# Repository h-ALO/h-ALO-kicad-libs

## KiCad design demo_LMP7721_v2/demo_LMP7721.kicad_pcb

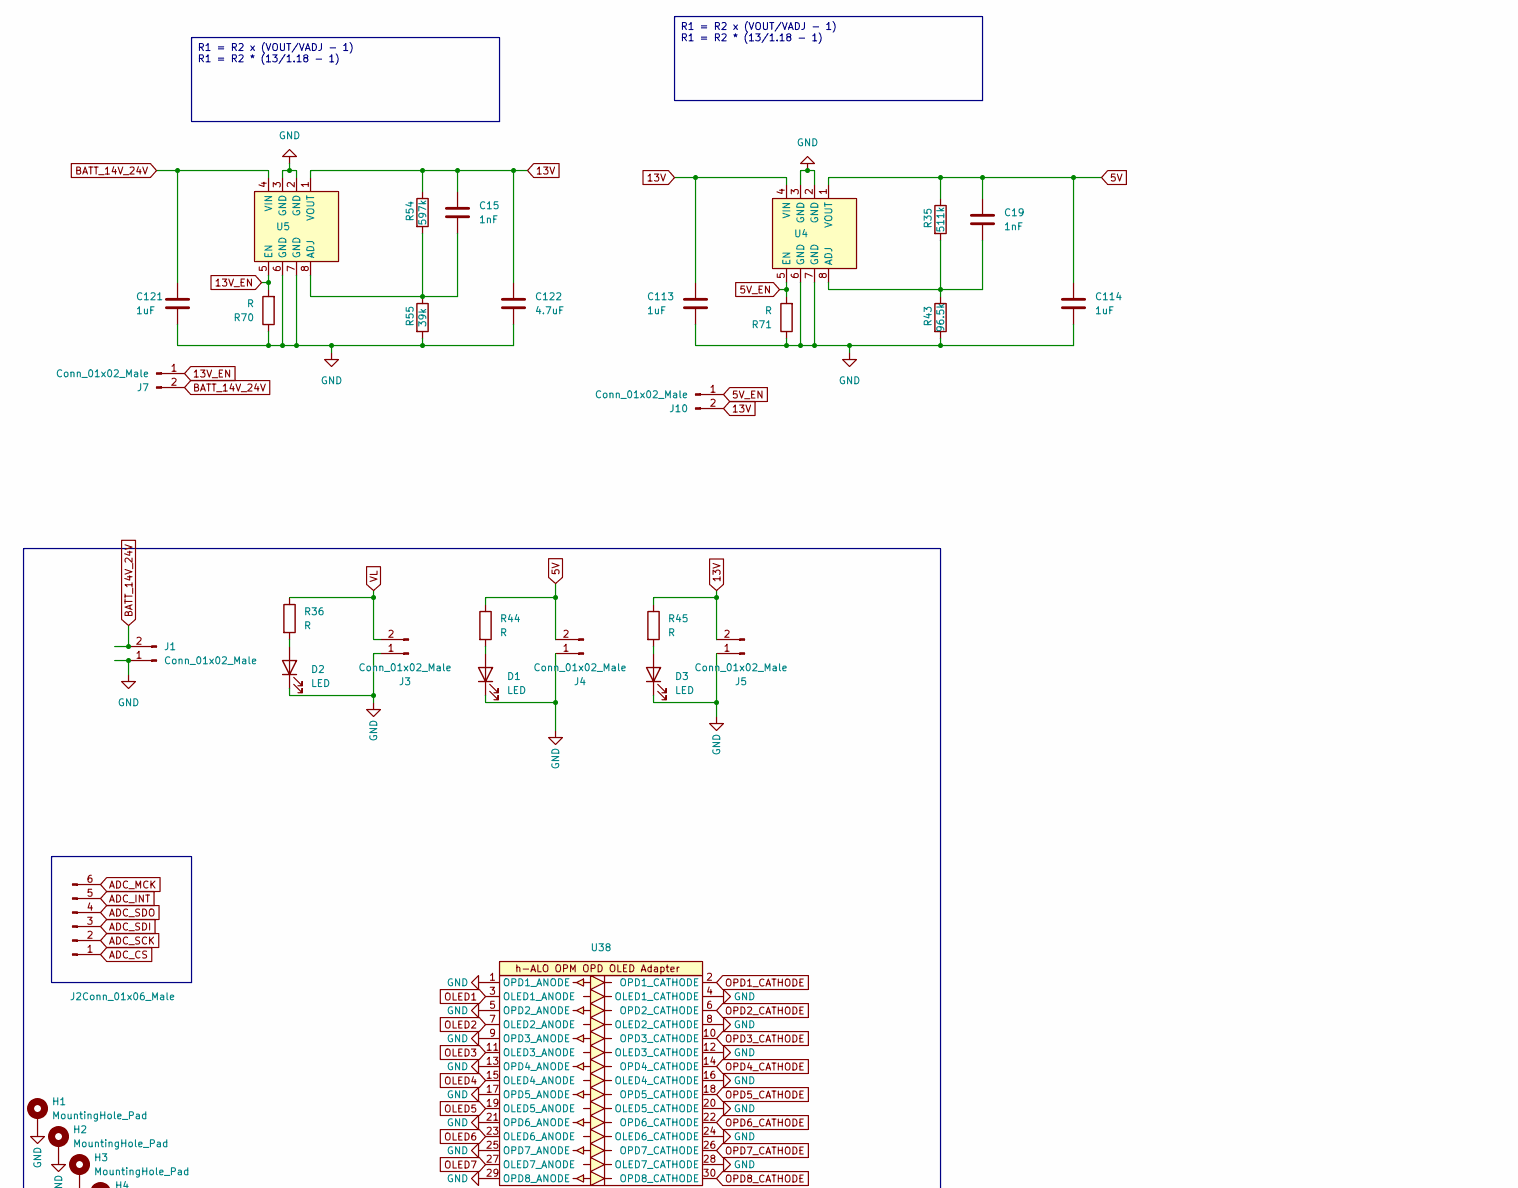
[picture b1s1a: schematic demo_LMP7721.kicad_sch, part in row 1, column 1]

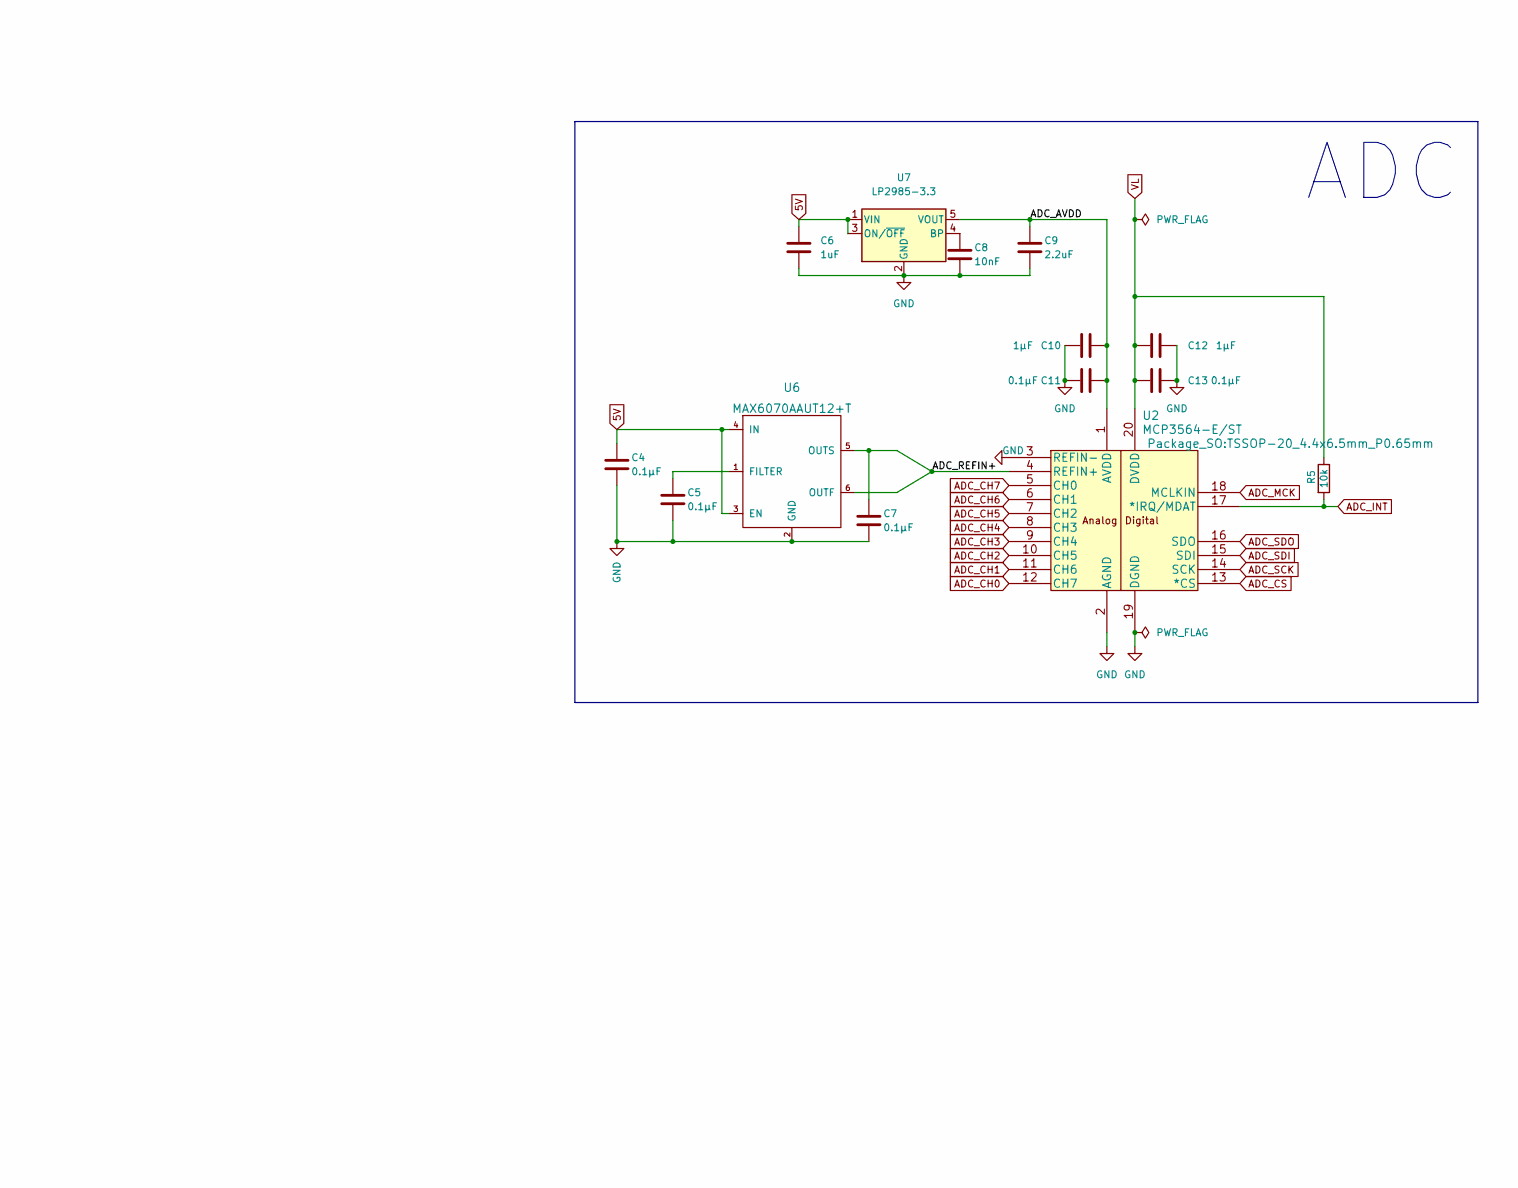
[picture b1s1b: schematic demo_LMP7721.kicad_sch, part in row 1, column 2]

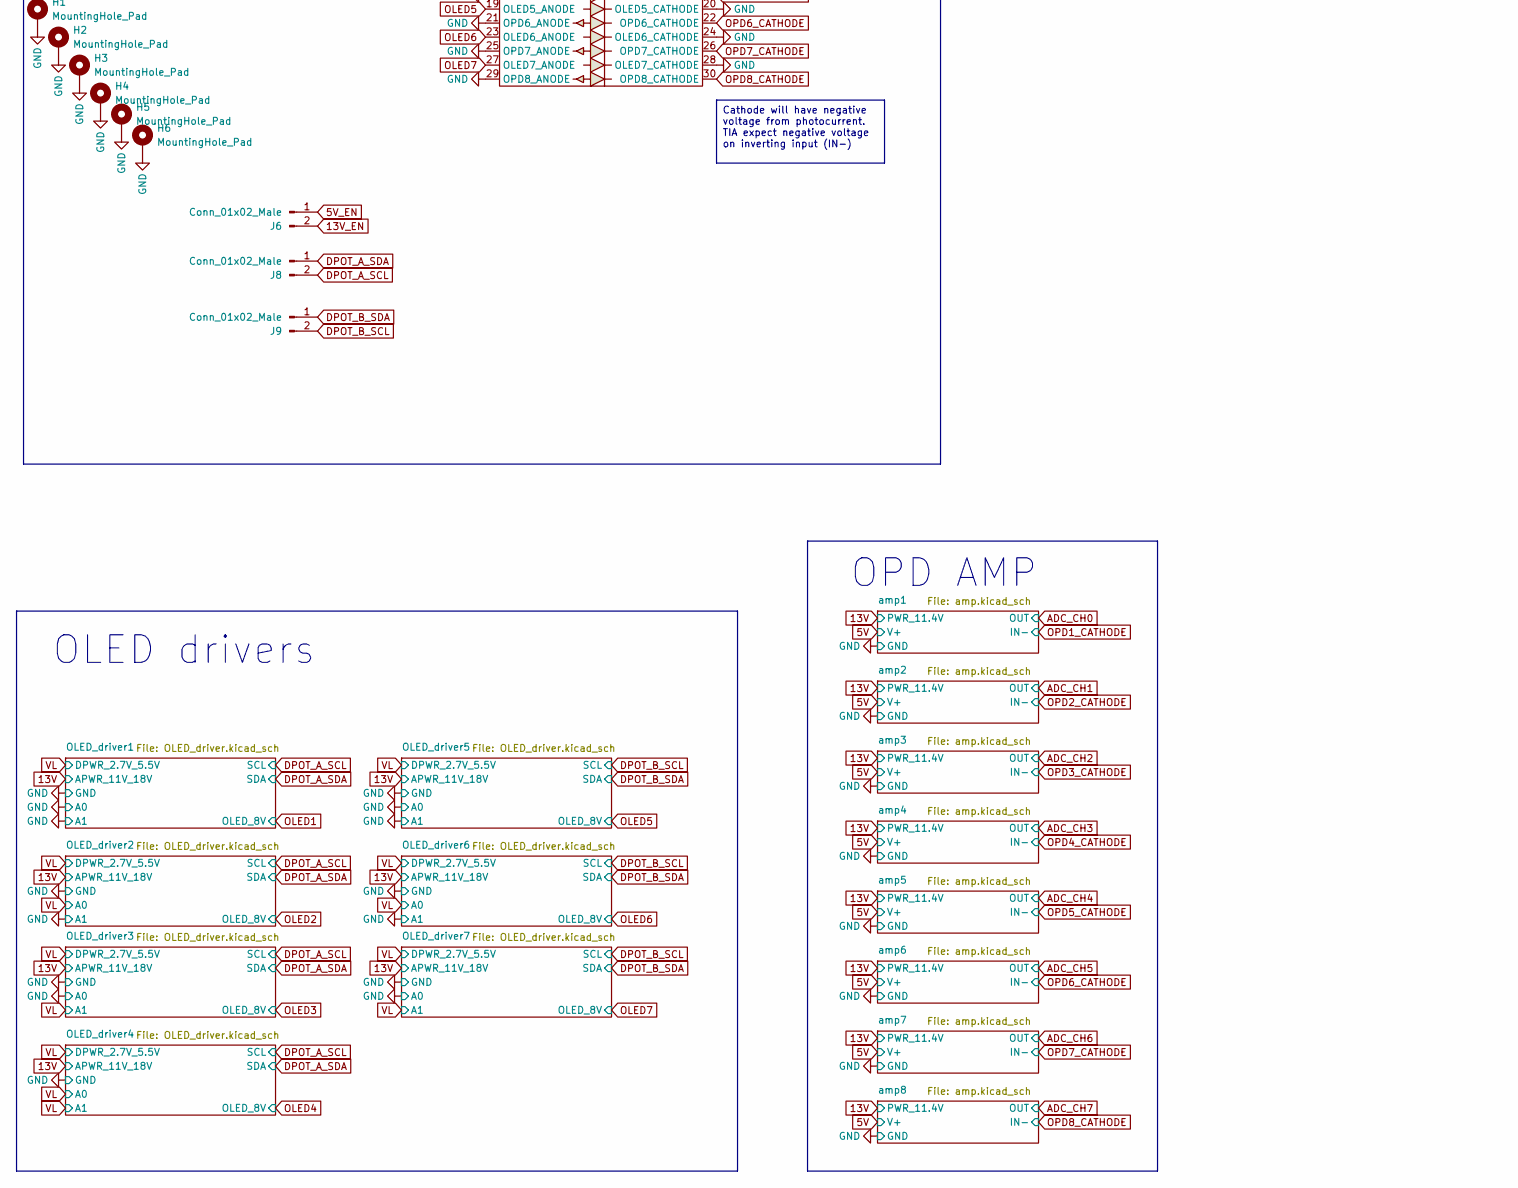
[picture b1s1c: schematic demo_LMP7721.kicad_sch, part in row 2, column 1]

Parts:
C4, C5, C7, C11, C13: 0.1µF; C_0603_1608Metric
C6: 1uF; C_0603_1608Metric
C8: 10nF; C_0603_1608Metric
C9: 2.2uF; C_0603_1608Metric
C10, C12: 1µF; C_0603_1608Metric
C15, C19: 1nF; C_0603_1608Metric
C113, C114, C121: 1uF; C_0805_2012Metric
C122: 4.7uF; C_0805_2012Metric
D1, D2, D3: LED; LED_0603_1608Metric
H1, H2, H3, H4, H5, H6: MountingHole_Pad; MountingHole_3.2mm_M3_Pad_Via
J1, J3, J4, J5, J6, J8, J9: Conn_01x02_Male; JST_XH_B2B-XH-A_1x02_P2.50mm_Vertical
J2: Conn_01x06_Male; JST_XH_B6B-XH-A_1x06_P2.50mm_Vertical
J7, J10: Conn_01x02_Male; PinHeader_1x02_P2.54mm_Vertical
R5: 10k; R_0603_1608Metric
R35: 511k; R_0603_1608Metric
R36, R44, R45, R70, R71: R; R_0603_1608Metric
R43: 96.5k; R_0603_1608Metric
R54: 597k; R_0603_1608Metric
R55: 39k; R_0603_1608Metric
U2: MCP3564-E/ST; TSSOP-20_4.4x6.5mm_P0.65mm
U4, U5: SOIC-8_3.9x4.9mm_P1.27mm
U6: MAX6070AAUT12+T; SOT-23-6
U7: LP2985-3.3; SOT-23-5
U38: OPM_Sensor_PinHeader_2x15_P2.54mm_Vertical

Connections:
5V: C4.1, C6.1, C19.1, C114.1, J4.2, R35.1, R44.1, U4.1 (VOUT), U6.3 (EN), U6.4 (IN), U7.1 (VIN), U7.3 (ON/~OFF); also elsewhere on the board
5V_EN: J6.1, J10.1, R71.2, U4.5 (EN)
13V: C15.1, C113.1, C122.1, J5.2, J10.2, R45.1, R54.1, U4.4 (VIN), U5.1 (VOUT); also elsewhere on the board
13V_EN: J6.2, J7.1, R70.2, U5.5 (EN)
/ADC_AVDD: C9.1, C10.2, C11.2, U2.1 (AVDD), U7.5 (VOUT)
/ADC_REFIN+: C7.1, U2.4 (REFIN+), U6.5 (OUTS), U6.6 (OUTF)
ADC_CH0: U2.12 (CH7); also elsewhere on the board
ADC_CH1: U2.11 (CH6); also elsewhere on the board
ADC_CH2: U2.10 (CH5); also elsewhere on the board
ADC_CH3: U2.9 (CH4); also elsewhere on the board
ADC_CH4: U2.8 (CH3); also elsewhere on the board
ADC_CH5: U2.7 (CH2); also elsewhere on the board
ADC_CH6: U2.6 (CH1); also elsewhere on the board
ADC_CH7: U2.5 (CH0); also elsewhere on the board
ADC_CS: J2.1, U2.13 (*CS)
ADC_INT: J2.5, R5.2, U2.17 (*IRQ/MDAT)
ADC_MCK: J2.6, U2.18 (MCLKIN)
ADC_SCK: J2.2, U2.14 (SCK)
ADC_SDI: J2.3, U2.15 (SDI)
ADC_SDO: J2.4, U2.16 (SDO)
BATT_14V_24V: C121.1, J1.2, J7.2, U5.4 (VIN)
DPOT_A_SCL: J8.2; also elsewhere on the board
DPOT_A_SDA: J8.1; also elsewhere on the board
DPOT_B_SCL: J9.2; also elsewhere on the board
DPOT_B_SDA: J9.1; also elsewhere on the board
GND: C4.2, C5.2, C6.2, C7.2, C8.2, C9.2, C10.1, C11.1, C12.2, C13.2, C113.2, C114.2, C121.2, C122.2, D1.1 (K), D2.1 (K), D3.1 (K), H1.1, H2.1, H3.1, H4.1, H5.1, H6.1, J1.1, J3.1, J4.1, J5.1, R43.2, R55.2, R70.1, R71.1, U2.2 (AGND), U2.3 (REFIN-), U2.19 (DGND), U4.2 (GND), U4.3 (GND), U4.6 (GND), U4.7 (GND), U5.2 (GND), U5.3 (GND), U5.6 (GND), U5.7 (GND), U6.2 (GND), U7.2 (GND), U38.1 (OPD1_ANODE), U38.4 (OLED1_CATHODE), U38.5 (OPD2_ANODE), U38.8 (OLED2_CATHODE), U38.9 (OPD3_ANODE), U38.12 (OLED3_CATHODE), U38.13 (OPD4_ANODE), U38.16 (OLED4_CATHODE), U38.17 (OPD5_ANODE), U38.20 (OLED5_CATHODE), U38.21 (OPD6_ANODE), U38.24 (OLED6_CATHODE), U38.25 (OPD7_ANODE), U38.28 (OLED7_CATHODE), U38.29 (OPD8_ANODE); also elsewhere on the board
unnamed: D1.2 (A), R44.2
unnamed: D2.2 (A), R36.2
unnamed: D3.2 (A), R45.2
unnamed: C19.2, R35.2, R43.1, U4.8 (ADJ)
unnamed: C15.2, R54.2, R55.1, U5.8 (ADJ)
unnamed: C5.1, U6.1 (FILTER)
unnamed: C8.1, U7.4 (BP)
OLED1: U38.3 (OLED1_ANODE); also elsewhere on the board
OLED2: U38.7 (OLED2_ANODE); also elsewhere on the board
OLED3: U38.11 (OLED3_ANODE); also elsewhere on the board
OLED4: U38.15 (OLED4_ANODE); also elsewhere on the board
OLED5: U38.19 (OLED5_ANODE); also elsewhere on the board
OLED6: U38.23 (OLED6_ANODE); also elsewhere on the board
OLED7: U38.27 (OLED7_ANODE); also elsewhere on the board
OPD1_CATHODE: U38.2 (OPD1_CATHODE); also elsewhere on the board
OPD2_CATHODE: U38.6 (OPD2_CATHODE); also elsewhere on the board
OPD3_CATHODE: U38.10 (OPD3_CATHODE); also elsewhere on the board
OPD4_CATHODE: U38.14 (OPD4_CATHODE); also elsewhere on the board
OPD5_CATHODE: U38.18 (OPD5_CATHODE); also elsewhere on the board
OPD6_CATHODE: U38.22 (OPD6_CATHODE); also elsewhere on the board
OPD7_CATHODE: U38.26 (OPD7_CATHODE); also elsewhere on the board
OPD8_CATHODE: U38.30 (OPD8_CATHODE); also elsewhere on the board
VL: C12.1, C13.1, J3.2, R5.1, R36.1, U2.20 (DVDD); also elsewhere on the board

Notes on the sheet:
R1 = R2 x (VOUT/VADJ - 1) R1 = R2 * (13/1.18 - 1)
Cathode will have negative voltage from photocurrent. TIA expect negative voltage on inverting input (IN-)
OPD AMP
ADC
OLED drivers

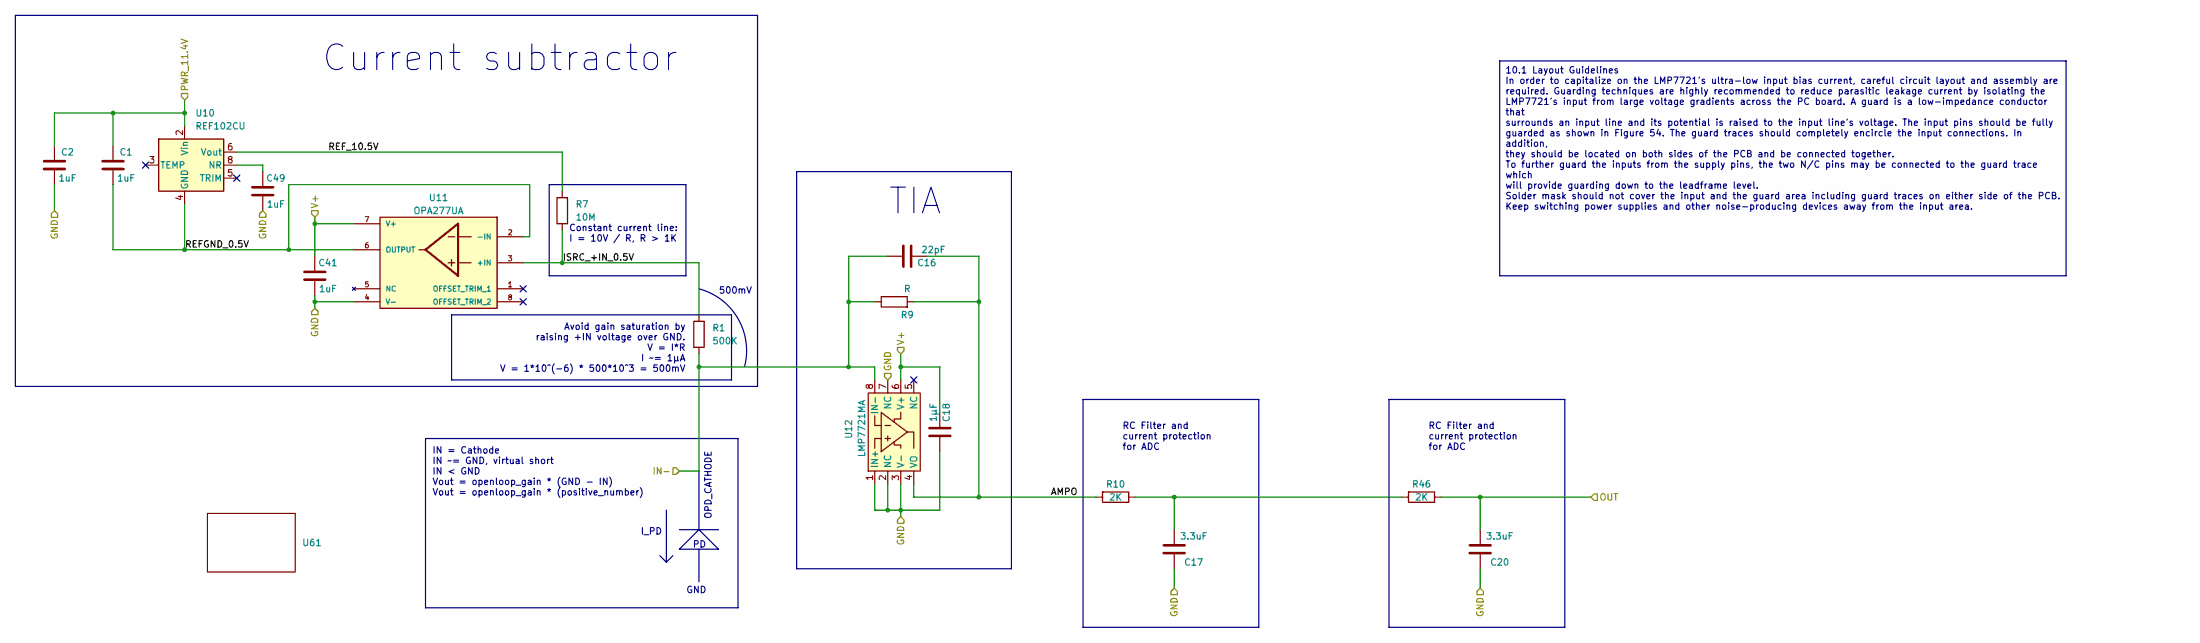
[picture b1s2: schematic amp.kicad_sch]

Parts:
C1, C2, C41, C49: 1uF; C_0603_1608Metric
C16: 22pF; FB_C_0603_1608Metric
C17, C20: 3.3uF; C_0603_1608Metric
C18: 1µF; C_0603_1608Metric
R1: 500K; TIA_R_0603_1608Metric
R7: 10M; R_0603_1608Metric
R9: R; FB_R_1206_3216Metric
R10, R46: 2K; R_0603_1608Metric
U10: REF102CU; SOIC-8_3.9x4.9mm_P1.27mm
U11: OPA277UA; TIA_OPA277_SOIC-8_3.9x4.9mm_P1.27mm; PARTREV 02/2019
U12: LMP7721MA; TIA_OPAMP_SOIC-8_3.9x4.9mm_P1.27mm
U61: OPD_TIA_Outline

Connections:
5V: C18.2, C41.2, U11.7 (V+), U12.6 (V+); also elsewhere on the board
13V: C1.2, C2.2, U10.2 (Vin); also elsewhere on the board
/amp1/AMPO: C16.2, R9.2, R10.2, U12.4 (VO)
/amp1/ISRC_+IN_0.5V: R1.2, R7.1, U11.3 (+IN)
/amp1/REFGND_0.5V: C1.1, U10.4 (GND), U11.2 (-IN), U11.6 (OUTPUT)
/amp1/REF_10.5V: R7.2, U10.6 (Vout)
ADC_CH0: C20.2, R46.1; also elsewhere on the board
GND: C2.1, C17.1, C18.1, C20.1, C41.1, C49.1, U11.4 (V-), U12.1 (IN+), U12.2 (NC), U12.3 (V-), U12.7 (NC); also elsewhere on the board
unnamed: C17.2, R10.1, R46.2
unnamed: C49.2, U10.8 (NR)
OPD1_CATHODE: C16.1, R1.1, R9.1, U12.8 (IN-); also elsewhere on the board

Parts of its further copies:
C21, C28, C40, C53, C97, C104, C111, C112, C115, C116, C117, C118, C119, C120: 3.3uF; C_0603_1608Metric
C22, C23, C24, C25, C29, C35, C36, C37, C42, C43, C44, C45, C55, C57, C61, C62, C84, C85, C86, C87, C98, C99, C100, C101, C105, C106, C107, C108: 1uF; C_0603_1608Metric
C26, C38, C47, C63, C88, C102, C109: 22pF; FB_C_0603_1608Metric
C27, C39, C51, C64, C96, C103, C110: 1µF; C_0603_1608Metric
R2, R14, R19, R25, R27, R30, R34: 10M; R_0603_1608Metric
R3, R15, R21, R26, R31, R37, R40: 500K; TIA_R_0603_1608Metric
R11, R17, R22, R28, R32, R38, R41: R; FB_R_1206_3216Metric
R13, R18, R23, R29, R33, R39, R42, R47, R48, R49, R50, R51, R52, R53: 2K; R_0603_1608Metric
U3, U17, U20, U23, U45, U48, U51: REF102CU; SOIC-8_3.9x4.9mm_P1.27mm
U15, U18, U21, U24, U46, U49, U52: OPA277UA; TIA_OPA277_SOIC-8_3.9x4.9mm_P1.27mm; PARTREV 02/2019
U16, U19, U22, U36, U47, U50, U53: LMP7721MA; TIA_OPAMP_SOIC-8_3.9x4.9mm_P1.27mm
U62, U63, U64, U65, U66, U67, U68: OPD_TIA_Outline

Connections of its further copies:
5V: C25.2, C27.2, C37.2, C39.2, C45.2, C51.2, C62.2, C64.2, C87.2, C96.2, C101.2, C103.2, C108.2, C110.2, U15.7 (V+), U16.6 (V+), U18.7 (V+), U19.6 (V+), U21.7 (V+), U22.6 (V+), U24.7 (V+), U36.6 (V+), U46.7 (V+), U47.6 (V+), U49.7 (V+), U50.6 (V+), U52.7 (V+), U53.6 (V+); also elsewhere on the board
13V: C22.2, C23.2, C29.2, C35.2, C42.2, C43.2, C55.2, C57.2, C84.2, C85.2, C98.2, C99.2, C105.2, C106.2, U3.2 (Vin), U17.2 (Vin), U20.2 (Vin), U23.2 (Vin), U45.2 (Vin), U48.2 (Vin), U51.2 (Vin); also elsewhere on the board
/amp2/AMPO: C26.2, R11.2, R13.2, U16.4 (VO)
/amp2/ISRC_+IN_0.5V: R2.1, R3.2, U15.3 (+IN)
/amp2/REFGND_0.5V: C23.1, U3.4 (GND), U15.2 (-IN), U15.6 (OUTPUT)
/amp2/REF_10.5V: R2.2, U3.6 (Vout)
/amp3/AMPO: C38.2, R17.2, R18.2, U19.4 (VO)
/amp3/ISRC_+IN_0.5V: R14.1, R15.2, U18.3 (+IN)
/amp3/REFGND_0.5V: C35.1, U17.4 (GND), U18.2 (-IN), U18.6 (OUTPUT)
/amp3/REF_10.5V: R14.2, U17.6 (Vout)
/amp4/AMPO: C47.2, R22.2, R23.2, U22.4 (VO)
/amp4/ISRC_+IN_0.5V: R19.1, R21.2, U21.3 (+IN)
/amp4/REFGND_0.5V: C43.1, U20.4 (GND), U21.2 (-IN), U21.6 (OUTPUT)
/amp4/REF_10.5V: R19.2, U20.6 (Vout)
/amp5/AMPO: C63.2, R28.2, R29.2, U36.4 (VO)
/amp5/ISRC_+IN_0.5V: R25.1, R26.2, U24.3 (+IN)
/amp5/REFGND_0.5V: C57.1, U23.4 (GND), U24.2 (-IN), U24.6 (OUTPUT)
/amp5/REF_10.5V: R25.2, U23.6 (Vout)
/amp6/AMPO: C102.2, R32.2, R33.2, U50.4 (VO)
/amp6/ISRC_+IN_0.5V: R30.1, R31.2, U49.3 (+IN)
/amp6/REFGND_0.5V: C99.1, U48.4 (GND), U49.2 (-IN), U49.6 (OUTPUT)
/amp6/REF_10.5V: R30.2, U48.6 (Vout)
/amp7/AMPO: C109.2, R38.2, R39.2, U53.4 (VO)
/amp7/ISRC_+IN_0.5V: R34.1, R37.2, U52.3 (+IN)
/amp7/REFGND_0.5V: C106.1, U51.4 (GND), U52.2 (-IN), U52.6 (OUTPUT)
/amp7/REF_10.5V: R34.2, U51.6 (Vout)
/amp8/AMPO: C88.2, R41.2, R42.2, U47.4 (VO)
/amp8/ISRC_+IN_0.5V: R27.1, R40.2, U46.3 (+IN)
/amp8/REFGND_0.5V: C85.1, U45.4 (GND), U46.2 (-IN), U46.6 (OUTPUT)
/amp8/REF_10.5V: R27.2, U45.6 (Vout)
ADC_CH1: C21.2, R47.1; also elsewhere on the board
ADC_CH2: C115.2, R48.1; also elsewhere on the board
ADC_CH3: C116.2, R49.1; also elsewhere on the board
ADC_CH4: C117.2, R50.1; also elsewhere on the board
ADC_CH5: C118.2, R51.1; also elsewhere on the board
ADC_CH6: C119.2, R52.1; also elsewhere on the board
ADC_CH7: C120.2, R53.1; also elsewhere on the board
GND: C21.1, C22.1, C24.1, C25.1, C27.1, C28.1, C29.1, C36.1, C37.1, C39.1, C40.1, C42.1, C44.1, C45.1, C51.1, C53.1, C55.1, C61.1, C62.1, C64.1, C84.1, C86.1, C87.1, C96.1, C97.1, C98.1, C100.1, C101.1, C103.1, C104.1, C105.1, C107.1, C108.1, C110.1, C111.1, C112.1, C115.1, C116.1, C117.1, C118.1, C119.1, C120.1, U15.4 (V-), U16.1 (IN+), U16.2 (NC), U16.3 (V-), U16.7 (NC), U18.4 (V-), U19.1 (IN+), U19.2 (NC), U19.3 (V-), U19.7 (NC), U21.4 (V-), U22.1 (IN+), U22.2 (NC), U22.3 (V-), U22.7 (NC), U24.4 (V-), U36.1 (IN+), U36.2 (NC), U36.3 (V-), U36.7 (NC), U46.4 (V-), U47.1 (IN+), U47.2 (NC), U47.3 (V-), U47.7 (NC), U49.4 (V-), U50.1 (IN+), U50.2 (NC), U50.3 (V-), U50.7 (NC), U52.4 (V-), U53.1 (IN+), U53.2 (NC), U53.3 (V-), U53.7 (NC); also elsewhere on the board
unnamed: C28.2, R13.1, R47.2
unnamed: C40.2, R18.1, R48.2
unnamed: C53.2, R23.1, R49.2
unnamed: C97.2, R29.1, R50.2
unnamed: C104.2, R33.1, R51.2
unnamed: C111.2, R39.1, R52.2
unnamed: C112.2, R42.1, R53.2
unnamed: C24.2, U3.8 (NR)
unnamed: C36.2, U17.8 (NR)
unnamed: C44.2, U20.8 (NR)
unnamed: C61.2, U23.8 (NR)
unnamed: C86.2, U45.8 (NR)
unnamed: C100.2, U48.8 (NR)
unnamed: C107.2, U51.8 (NR)
OPD2_CATHODE: C26.1, R3.1, R11.1, U16.8 (IN-); also elsewhere on the board
OPD3_CATHODE: C38.1, R15.1, R17.1, U19.8 (IN-); also elsewhere on the board
OPD4_CATHODE: C47.1, R21.1, R22.1, U22.8 (IN-); also elsewhere on the board
OPD5_CATHODE: C63.1, R26.1, R28.1, U36.8 (IN-); also elsewhere on the board
OPD6_CATHODE: C102.1, R31.1, R32.1, U50.8 (IN-); also elsewhere on the board
OPD7_CATHODE: C109.1, R37.1, R38.1, U53.8 (IN-); also elsewhere on the board
OPD8_CATHODE: C88.1, R40.1, R41.1, U47.8 (IN-); also elsewhere on the board

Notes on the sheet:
10.1 Layout Guidelines In order to capitalize on the LMP7721's ultra-low input bias current, careful circuit layout and assembly are required. Guarding techniques are highly recommended to reduce parasitic leakage current by isolating the LMP7721's input from large voltage gradients across the PC b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
I_PD
Constant current line: I = 10V / R, R > 1K
TIA
RC Filter and current protection for ADC
GND
Avoid gain saturation by raising +IN voltage over GND. V = I*R I ~= 1µA V = 1*10^(-6) * 500*10^3 = 500mV
IN = Cathode IN ~= GND, virtual short IN < GND Vout = openloop_gain * (GND - IN) Vout = openloop_gain * (positive_number)
500mV
OPD_CATHODE
Current subtractor

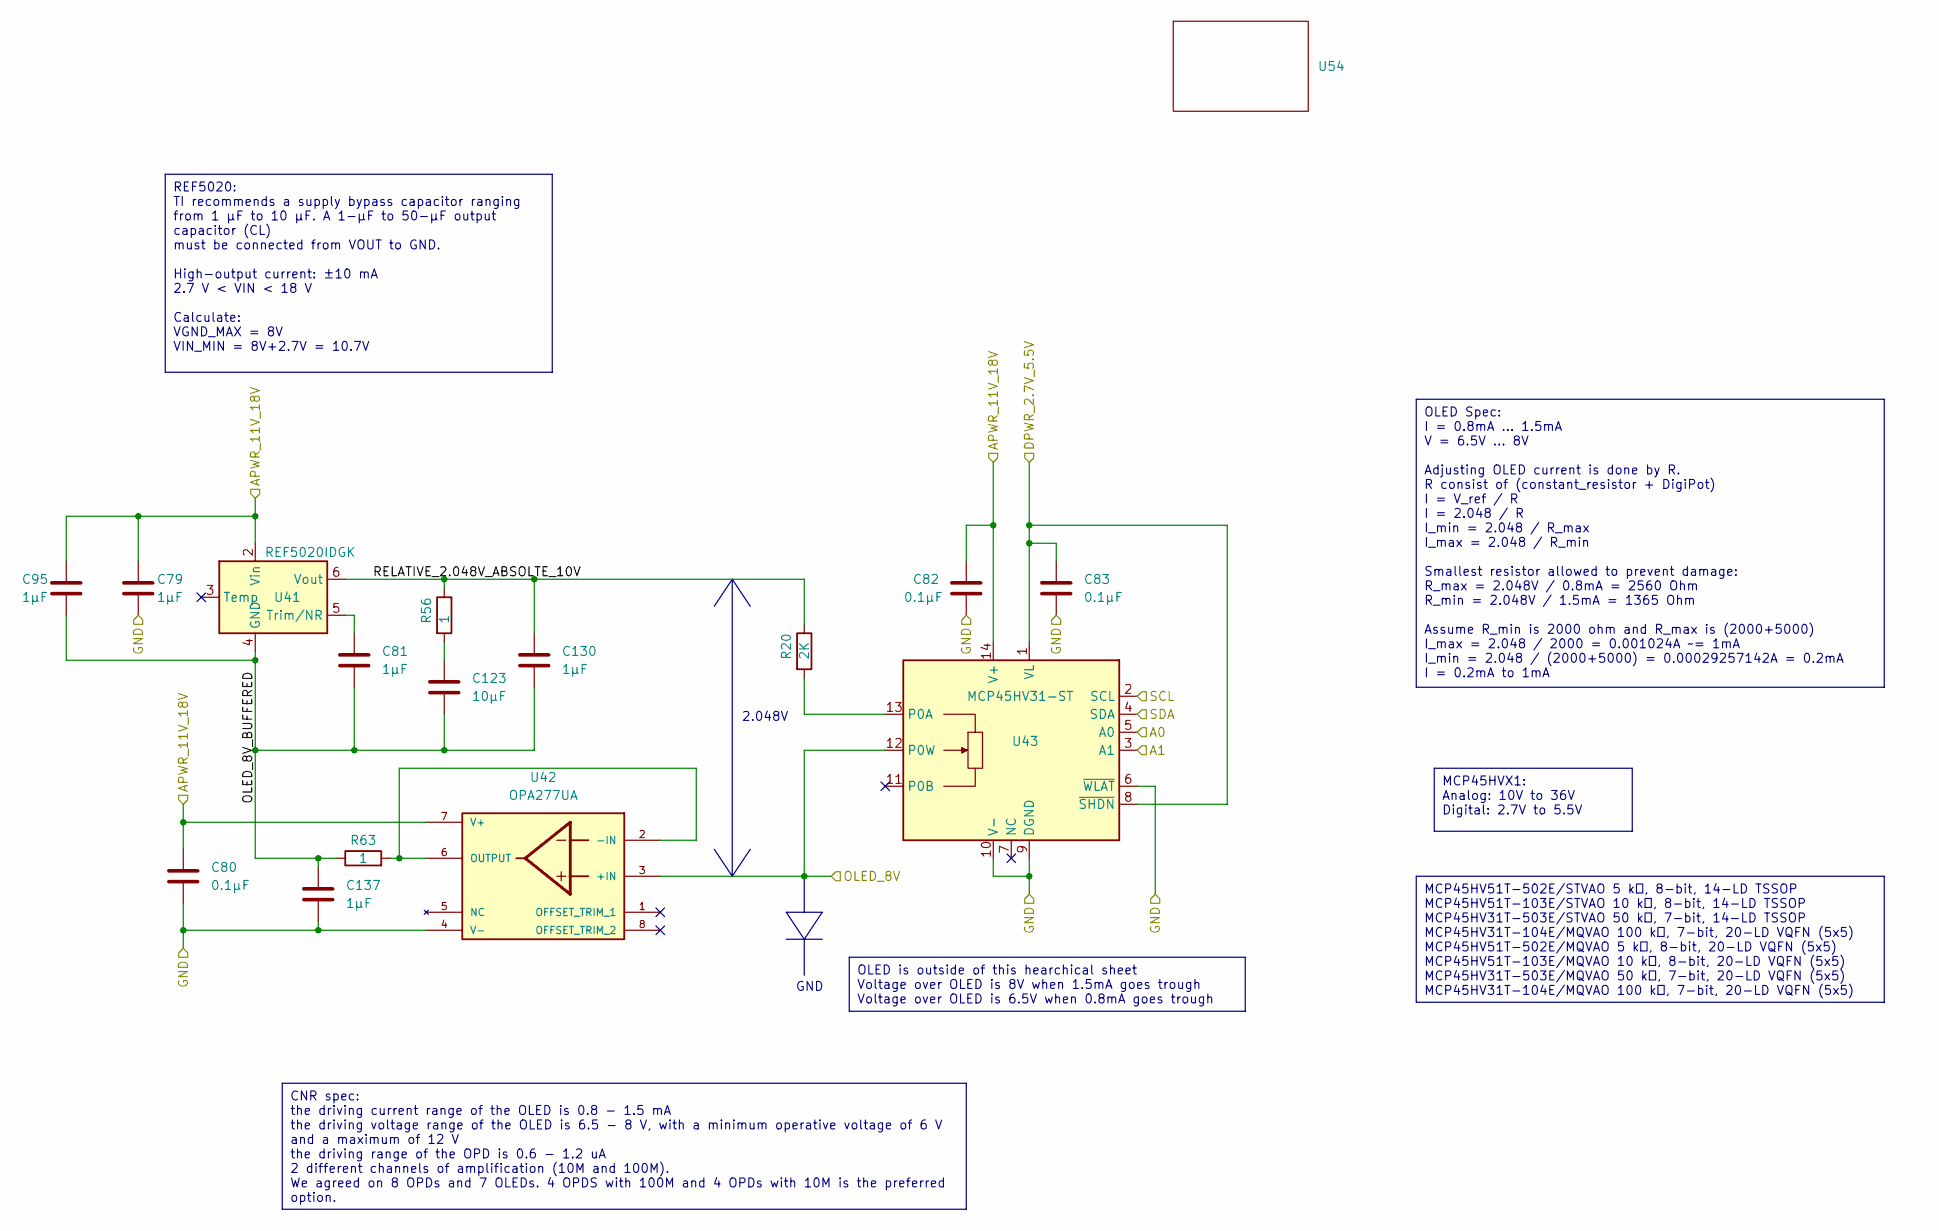
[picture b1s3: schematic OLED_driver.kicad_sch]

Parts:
C79, C81, C95, C130, C137: 1µF; C_0603_1608Metric
C80, C82, C83: 0.1μF; C_0603_1608Metric
C123: 10µF; C_1206_3216Metric
R20: 2K; R_0603_1608Metric
R56, R63: 1; R_0603_1608Metric
U41: REF5020IDGK; MSOP-8_3x3mm_P0.65mm
U42: OPA277UA; SOIC-8_3.9x4.9mm_P1.27mm; PARTREV 02/2019
U43: MCP45HV31-ST; TSSOP-14_4.4x5mm_P0.65mm
U54: OLED_Driver_Outline

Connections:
13V: C79.1, C80.1, C82.1, C95.1, U41.2 (Vin), U42.7 (V+), U43.14 (V+); also elsewhere on the board
/OLED_driver1/OLED_8V_BUFFERED: C81.2, C95.2, C123.2, C130.2, C137.1, R63.1, U41.4 (GND)
/OLED_driver1/RELATIVE_2.048V_ABSOLTE_10V: C130.1, R20.1, R56.1, U41.6 (Vout)
DPOT_A_SCL: U43.2 (SCL); also elsewhere on the board
DPOT_A_SDA: U43.4 (SDA); also elsewhere on the board
GND: C79.2, C80.2, C82.2, C83.2, C137.2, U42.4 (V-), U43.3 (A1), U43.5 (A0), U43.6 (~WLAT), U43.9 (DGND), U43.10 (V-); also elsewhere on the board
unnamed: C123.1, R56.2
unnamed: C81.1, U41.5 (Trim/NR)
unnamed: R63.2, U42.2 (-IN), U42.6 (OUTPUT)
unnamed: R20.2, U43.13 (P0A)
OLED1: U42.3 (+IN), U43.12 (P0W); also elsewhere on the board
VL: C83.1, U43.1 (VL), U43.8 (~SHDN); also elsewhere on the board

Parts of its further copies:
C3, C30, C33, C46, C52, C56, C60, C66, C69, C71, C74, C76, C89, C90, C91, C92, C93, C94, C131, C132, C133, C134, C135, C136, C138, C139, C140, C141, C142, C143: 1µF; C_0603_1608Metric
C14, C31, C32, C34, C48, C50, C54, C58, C59, C65, C67, C68, C70, C72, C73, C75, C77, C78: 0.1μF; C_0603_1608Metric
C124, C125, C126, C127, C128, C129: 10µF; C_1206_3216Metric
R4, R6, R8, R12, R16, R24: 2K; R_0603_1608Metric
R57, R58, R59, R60, R61, R62, R64, R65, R66, R67, R68, R69: 1; R_0603_1608Metric
U1, U25, U28, U31, U34, U39: REF5020IDGK; MSOP-8_3x3mm_P0.65mm
U8, U26, U29, U32, U35, U40: OPA277UA; SOIC-8_3.9x4.9mm_P1.27mm; PARTREV 02/2019
U9, U27, U30, U33, U37, U44: MCP45HV31-ST; TSSOP-14_4.4x5mm_P0.65mm
U55, U56, U57, U58, U59, U60: OLED_Driver_Outline

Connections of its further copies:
13V: C3.1, C14.1, C31.1, C33.1, C34.1, C48.1, C52.1, C54.1, C58.1, C60.1, C65.1, C67.1, C69.1, C70.1, C72.1, C74.1, C75.1, C77.1, C89.1, C90.1, C91.1, C92.1, C93.1, C94.1, U1.2 (Vin), U8.7 (V+), U9.14 (V+), U25.2 (Vin), U26.7 (V+), U27.14 (V+), U28.2 (Vin), U29.7 (V+), U30.14 (V+), U31.2 (Vin), U32.7 (V+), U33.14 (V+), U34.2 (Vin), U35.7 (V+), U37.14 (V+), U39.2 (Vin), U40.7 (V+), U44.14 (V+); also elsewhere on the board
/OLED_driver2/OLED_8V_BUFFERED: C30.2, C89.2, C124.2, C131.2, C138.1, R64.1, U1.4 (GND)
/OLED_driver2/RELATIVE_2.048V_ABSOLTE_10V: C131.1, R4.1, R57.1, U1.6 (Vout)
/OLED_driver3/OLED_8V_BUFFERED: C46.2, C90.2, C125.2, C132.2, C139.1, R65.1, U25.4 (GND)
/OLED_driver3/RELATIVE_2.048V_ABSOLTE_10V: C132.1, R6.1, R58.1, U25.6 (Vout)
/OLED_driver4/OLED_8V_BUFFERED: C56.2, C91.2, C126.2, C133.2, C140.1, R66.1, U28.4 (GND)
/OLED_driver4/RELATIVE_2.048V_ABSOLTE_10V: C133.1, R8.1, R59.1, U28.6 (Vout)
/OLED_driver5/OLED_8V_BUFFERED: C71.2, C93.2, C127.2, C134.2, C141.1, R67.1, U34.4 (GND)
/OLED_driver5/RELATIVE_2.048V_ABSOLTE_10V: C134.1, R16.1, R60.1, U34.6 (Vout)
/OLED_driver6/OLED_8V_BUFFERED: C76.2, C94.2, C128.2, C135.2, C142.1, R68.1, U39.4 (GND)
/OLED_driver6/RELATIVE_2.048V_ABSOLTE_10V: C135.1, R24.1, R61.1, U39.6 (Vout)
/OLED_driver7/OLED_8V_BUFFERED: C66.2, C92.2, C129.2, C136.2, C143.1, R69.1, U31.4 (GND)
/OLED_driver7/RELATIVE_2.048V_ABSOLTE_10V: C136.1, R12.1, R62.1, U31.6 (Vout)
DPOT_A_SCL: U9.2 (SCL), U27.2 (SCL), U30.2 (SCL); also elsewhere on the board
DPOT_A_SDA: U9.4 (SDA), U27.4 (SDA), U30.4 (SDA); also elsewhere on the board
DPOT_B_SCL: U33.2 (SCL), U37.2 (SCL), U44.2 (SCL); also elsewhere on the board
DPOT_B_SDA: U33.4 (SDA), U37.4 (SDA), U44.4 (SDA); also elsewhere on the board
GND: C3.2, C14.2, C31.2, C32.2, C33.2, C34.2, C48.2, C50.2, C52.2, C54.2, C58.2, C59.2, C60.2, C65.2, C67.2, C68.2, C69.2, C70.2, C72.2, C73.2, C74.2, C75.2, C77.2, C78.2, C138.2, C139.2, C140.2, C141.2, C142.2, C143.2, U8.4 (V-), U9.3 (A1), U9.6 (~WLAT), U9.9 (DGND), U9.10 (V-), U26.4 (V-), U27.5 (A0), U27.6 (~WLAT), U27.9 (DGND), U27.10 (V-), U29.4 (V-), U30.6 (~WLAT), U30.9 (DGND), U30.10 (V-), U32.4 (V-), U33.5 (A0), U33.6 (~WLAT), U33.9 (DGND), U33.10 (V-), U35.4 (V-), U37.3 (A1), U37.5 (A0), U37.6 (~WLAT), U37.9 (DGND), U37.10 (V-), U40.4 (V-), U44.3 (A1), U44.6 (~WLAT), U44.9 (DGND), U44.10 (V-); also elsewhere on the board
unnamed: C124.1, R57.2
unnamed: C125.1, R58.2
unnamed: C126.1, R59.2
unnamed: C127.1, R60.2
unnamed: C128.1, R61.2
unnamed: C129.1, R62.2
unnamed: C30.1, U1.5 (Trim/NR)
unnamed: R64.2, U8.2 (-IN), U8.6 (OUTPUT)
unnamed: R4.2, U9.13 (P0A)
unnamed: C46.1, U25.5 (Trim/NR)
unnamed: R65.2, U26.2 (-IN), U26.6 (OUTPUT)
unnamed: R6.2, U27.13 (P0A)
unnamed: C56.1, U28.5 (Trim/NR)
unnamed: R66.2, U29.2 (-IN), U29.6 (OUTPUT)
unnamed: R8.2, U30.13 (P0A)
unnamed: C66.1, U31.5 (Trim/NR)
unnamed: R69.2, U32.2 (-IN), U32.6 (OUTPUT)
unnamed: R12.2, U33.13 (P0A)
unnamed: C71.1, U34.5 (Trim/NR)
unnamed: R67.2, U35.2 (-IN), U35.6 (OUTPUT)
unnamed: R16.2, U37.13 (P0A)
unnamed: C76.1, U39.5 (Trim/NR)
unnamed: R68.2, U40.2 (-IN), U40.6 (OUTPUT)
unnamed: R24.2, U44.13 (P0A)
OLED2: U8.3 (+IN), U9.12 (P0W); also elsewhere on the board
OLED3: U26.3 (+IN), U27.12 (P0W); also elsewhere on the board
OLED4: U29.3 (+IN), U30.12 (P0W); also elsewhere on the board
OLED5: U35.3 (+IN), U37.12 (P0W); also elsewhere on the board
OLED6: U40.3 (+IN), U44.12 (P0W); also elsewhere on the board
OLED7: U32.3 (+IN), U33.12 (P0W); also elsewhere on the board
VL: C32.1, C50.1, C59.1, C68.1, C73.1, C78.1, U9.1 (VL), U9.5 (A0), U9.8 (~SHDN), U27.1 (VL), U27.3 (A1), U27.8 (~SHDN), U30.1 (VL), U30.3 (A1), U30.5 (A0), U30.8 (~SHDN), U33.1 (VL), U33.3 (A1), U33.8 (~SHDN), U37.1 (VL), U37.8 (~SHDN), U44.1 (VL), U44.5 (A0), U44.8 (~SHDN); also elsewhere on the board

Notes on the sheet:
OLED is outside of this hearchical sheet Voltage over OLED is 8V when 1.5mA goes trough Voltage over OLED is 6.5V when 0.8mA goes trough
CNR spec: the driving current range of the OLED is 0.8 - 1.5 mA the driving voltage range of the OLED is 6.5 - 8 V, with a minimum operative voltage of 6 V and a maximum of 12 V the driving range of the OPD is 0.6 - 1.2 uA 2 different channels of amplification (10M and 100M). We agreed on 8 OPDs an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
MCP45HV51T-502E/STVAO 5 k, 8-bit, 14-LD TSSOP MCP45HV51T-103E/STVAO 10 k, 8-bit, 14-LD TSSOP MCP45HV31T-503E/STVAO 50 k, 7-bit, 14-LD TSSOP MCP45HV31T-104E/MQVAO 100 k, 7-bit, 20-LD VQFN (5x5) MCP45HV51T-502E/MQVAO 5 k, 8-bit, 20-LD VQFN (5x5) MCP45HV51T-103E/MQVAO 10 k, 8-bit, 20-LD VQFN (5x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
OLED Spec: I = 0.8mA ... 1.5mA V = 6.5V ... 8V Adjusting OLED current is done by R. R consist of (constant_resistor + DigiPot) I = V_ref / R I = 2.048 / R I_min = 2.048 / R_max I_max = 2.048 / R_min Smallest resistor allowed to prevent damage: R_max = 2.048V / 0.8mA = 2560 Ohm R_min = 2.048V / 1.5m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
REF5020: TI recommends a supply bypass capacitor ranging from 1 μF to 10 μF. A 1-μF to 50-μF output capacitor (CL) must be connected from VOUT to GND. High-output current: ±10 mA 2.7 V < VIN < 18 V Calculate: VGND_MAX = 8V VIN_MIN = 8V+2.7V = 10.7V
MCP45HVX1: Analog: 10V to 36V Digital: 2.7V to 5.5V
2.048V
GND

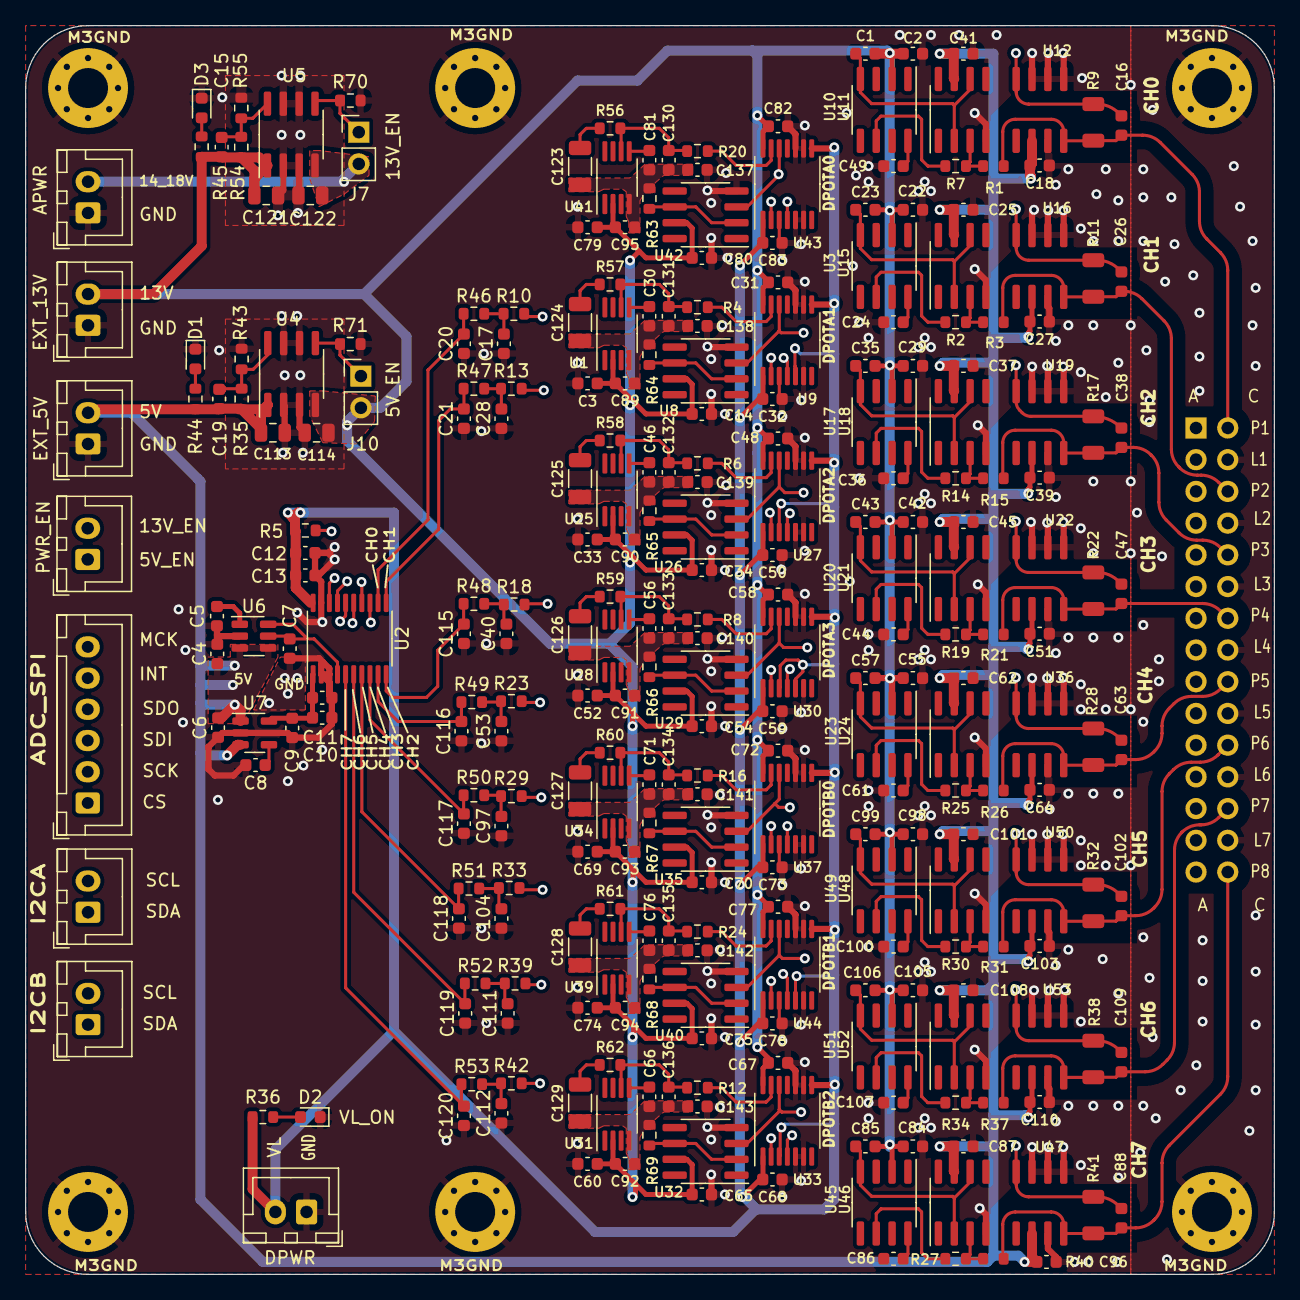
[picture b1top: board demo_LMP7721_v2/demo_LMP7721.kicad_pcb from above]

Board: 4 copper layers, 100.0 x 100.0 mm, 299 parts (0 on the bottom side), 139 nets.

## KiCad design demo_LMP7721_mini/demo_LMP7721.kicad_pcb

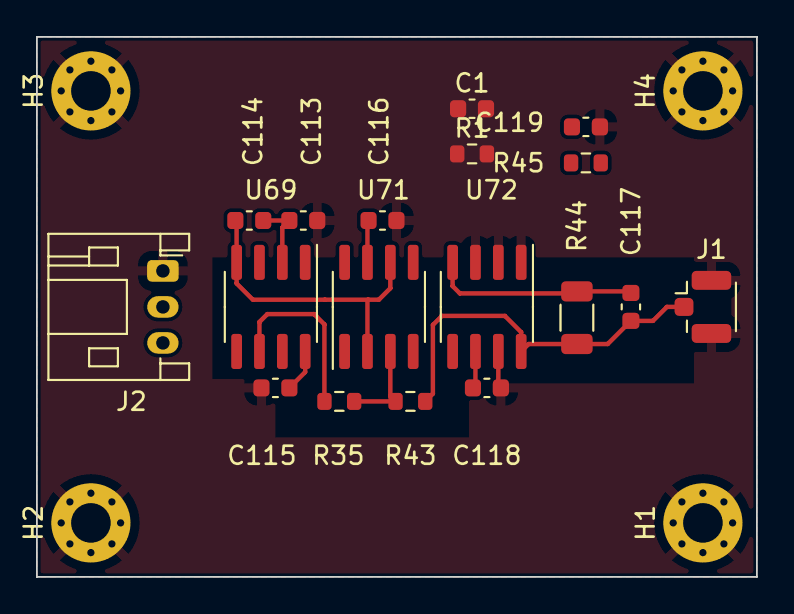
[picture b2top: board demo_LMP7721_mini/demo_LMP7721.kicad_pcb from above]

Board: 2 copper layers, 40.0 x 30.0 mm, 22 parts (0 on the bottom side), 11 nets.

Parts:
C1, C119: 3.3uF; C_0603_1608Metric
C113, C114, C115, C116: 1uF; C_0603_1608Metric
C117: 22pF; C_0603_1608Metric
C118: 1µF; C_0603_1608Metric
H1, H2, H3, H4: MountingHole_Pad; MountingHole_2.2mm_M2_Pad_Via
J1: Conn_01x02_Socket; U.FL_Hirose_U.FL-R-SMT-1_Vertical
J2: Conn_01x03_Socket; JST_PH_S3B-PH-K_1x03_P2.00mm_Horizontal
R1, R45: 2K; R_0603_1608Metric
R35: 10M; R_0603_1608Metric
R43: 500K; R_0603_1608Metric
R44: R; R_1206_3216Metric
U69: REF102CU; SOIC-8_3.9x4.9mm_P1.27mm
U71: OPA277UA; SOIC-8_3.9x4.9mm_P1.27mm
U72: LMP7721MA; SOIC-8_3.9x4.9mm_P1.27mm

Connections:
5V: C116.2, C118.2, J2.2, U71.7 (V+), U72.6 (V+)
12V: C113.2, C114.2, J2.3, U69.2 (Vin)
/AMPO: C117.2, R44.2, R45.2, U72.4 (VO)
/GND: C1.1, C113.1, C115.1, C116.1, C118.1, C119.1, H1.1, H2.1, H3.1, H4.1, J1.2, J2.1, U71.4 (V-), U72.1 (IN+), U72.2 (NC), U72.3 (V-), U72.7 (NC)
/IN-: C117.1, J1.1, R43.1, R44.1, U72.8 (IN-)
/ISRC_+IN_0.5V: R35.1, R43.2, U71.3 (+IN)
/OUT: C1.2, R1.1
/REFGND_0.5V: C114.1, U69.4 (GND), U71.2 (-IN), U71.6 (OUTPUT)
/REF_10.5V: R35.2, U69.6 (Vout)
unnamed: C119.2, R1.2, R45.1
unnamed: C115.2, U69.8 (NR)
